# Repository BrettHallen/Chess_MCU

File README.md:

# Chess Microcontrollers
Tinkering with electronic chess games.  I'm am useless at chess but it still fascinates me.<br>

Related videos:
- [LogiChess Part 1](https://youtu.be/34F9DbmAjUU)
- [LogiChess Part 2](https://youtu.be/Y_kRFhx9leI)

## [Tandy 1650](/Tandy_1650_Chess)
Information about the Tandy 1650 Computerised Portable Sensory Chess game.  It uses the SciSys TE1 which is 4KB LogiChess implemented on an Hitachi HD6301V microcontroller.<br>

## [VIC-20 Chess Co-processor](/VIC-20_LogiChess)
I had a thought to re-use the MCU in the Tandy 1650, the SciSys TE1 implementing 4KB LogiChess, as a "co-processor" for vintage 8-bit computers, for example the Commodore VIC-20.<br>

This isn't the same as simply having the game code on a cartridge as the VIC's CPU is still running the code.<br>

I was wondering if it would be interesting to have a dedicated microcontroller doing the "chess processing".  It might be beyond my capabilities but this is how you learn new things.<br>

Ultimately it might be easier to just use an ATmega MCU with a chess program running on it.  But let's see.

## [LogiChess-Arduino Testing](/LogiChess-Arduino_Mega_Shield_Testing)
As part of my work on trying to get LogiChess MCU working with a VIC-20, I will first do some investigation on how to interface with the SciSys TE-1 by using an Arduino.  If I can get that working then it might give me some idea how to get it working on the VIC.<br>

## [Chess Keypad](/Chess_Keypad)
In conjunction with the Arduino interfacing, I'm creating a keypad to replicate the original Tandy 1650 hardware to assist with testing.<br>

So ...
- Step 1: get the SciSys TE1 working with my chess keypad and the Arduino logging information
- Step 2: get the Arduino (in place of the VIC-20) working with the SciSys TE1
- Step 3: get the VIC-20 working with the SciSys TE1

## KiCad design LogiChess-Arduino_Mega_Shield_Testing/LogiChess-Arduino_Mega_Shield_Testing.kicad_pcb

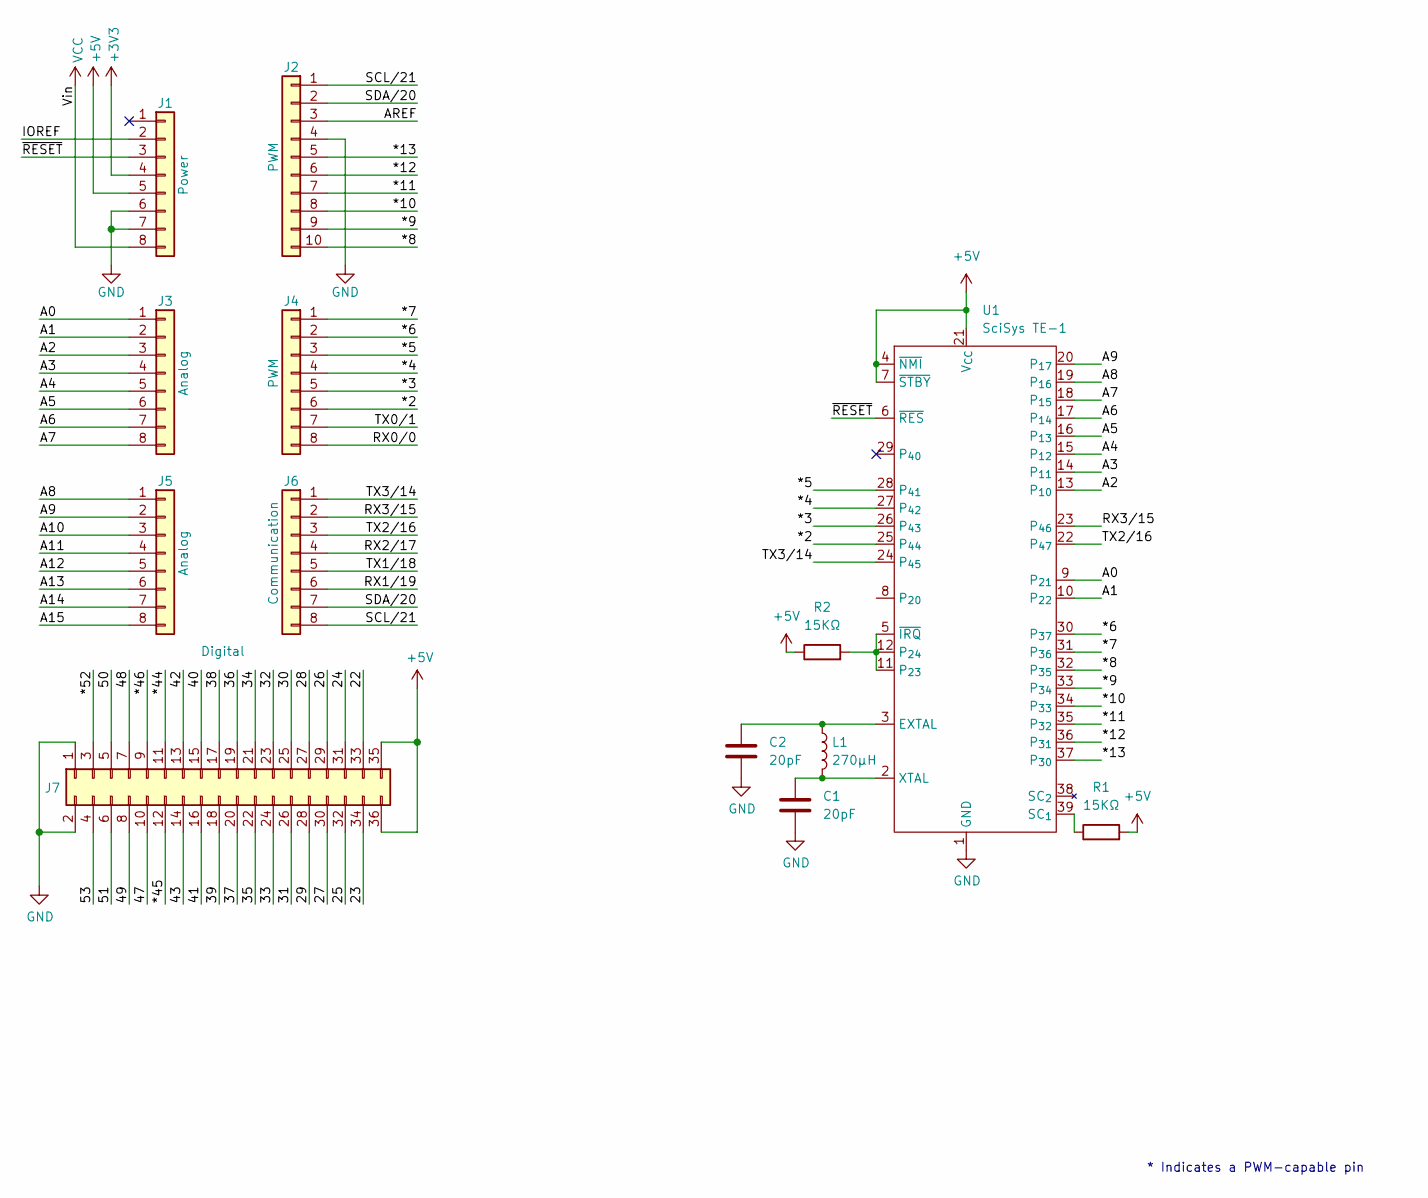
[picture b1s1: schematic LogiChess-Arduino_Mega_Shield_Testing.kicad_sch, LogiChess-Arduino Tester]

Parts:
C1, C2: 20pF; C_Disc_D3.8mm_W2.6mm_P2.50mm
J1: Power; PinSocket_1x08_P2.54mm_Vertical
J2: PWM; PinSocket_1x10_P2.54mm_Vertical
J3, J5: Analog; PinSocket_1x08_P2.54mm_Vertical
J4: PWM; PinSocket_1x08_P2.54mm_Vertical
J6: Communication; PinSocket_1x08_P2.54mm_Vertical
J7: Digital; PinSocket_2x18_P2.54mm_Vertical
L1: 270µH; L_Radial_D6.0mm_P4.00mm
R1, R2: 15KΩ; R_Axial_DIN0207_L6.3mm_D2.5mm_P7.62mm_Horizontal
U1: SciSys TE-1; DIP-40_W15.24mm

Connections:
+3V3: J1.4
+5V: J1.5, J7.35, J7.36, R1.2, R2.1, U1.4 (~NMI), U1.7 (~STBY), U1.21 (V_{CC})
/22: J7.33
/23: J7.34
/24: J7.31
/25: J7.32
/26: J7.29
/27: J7.30
/28: J7.27
/29: J7.28
/30: J7.25
/31: J7.26
/32: J7.23
/33: J7.24
/34: J7.21
/35: J7.22
/36: J7.19
/37: J7.20
/38: J7.17
/39: J7.18
/40: J7.15
/41: J7.16
/42: J7.13
/43: J7.14
/47: J7.10
/48: J7.7
/49: J7.8
/50: J7.5
/51: J7.6
/53: J7.4
/*2: J4.6, U1.25 (P_{44})
/*3: J4.5, U1.26 (P_{43})
/*4: J4.4, U1.27 (P_{42})
/*5: J4.3, U1.28 (P_{41})
/*6: J4.2, U1.30 (P_{37})
/*7: J4.1, U1.31 (P_{36})
/*8: J2.10, U1.32 (P_{35})
/*9: J2.9, U1.33 (P_{34})
/*10: J2.8, U1.34 (P_{33})
/*11: J2.7, U1.35 (P_{32})
/*12: J2.6, U1.36 (P_{31})
/*13: J2.5, U1.37 (P_{30})
/*44: J7.11
/*45: J7.12
/*46: J7.9
/*52: J7.3
/A0: J3.1, U1.9 (P_{21})
/A1: J3.2, U1.10 (P_{22})
/A2: J3.3, U1.13 (P_{10})
/A3: J3.4, U1.14 (P_{11})
/A4: J3.5, U1.15 (P_{12})
/A5: J3.6, U1.16 (P_{13})
/A6: J3.7, U1.17 (P_{14})
/A7: J3.8, U1.18 (P_{15})
/A8: J5.1, U1.19 (P_{16})
/A9: J5.2, U1.20 (P_{17})
/A10: J5.3
/A11: J5.4
/A12: J5.5
/A13: J5.6
/A14: J5.7
/A15: J5.8
/AREF: J2.3
/IOREF: J1.2
/RX0/0: J4.8
/RX1/19: J6.6
/RX2/17: J6.4
/RX3/15: J6.2, U1.23 (P_{46})
/SCL/21: J2.1, J6.8
/SDA/20: J2.2, J6.7
/TX0/1: J4.7
/TX1/18: J6.5
/TX2/16: J6.3, U1.22 (P_{47})
/TX3/14: J6.1, U1.24 (P_{45})
/~RESET: J1.3, U1.6 (~RES)
GND: C1.2, C2.2, J1.6, J1.7, J2.4, J7.1, J7.2, U1.1 (GND)
unnamed: C2.1, L1.1, U1.3 (EXTAL)
unnamed: R2.2, U1.5 (~IRQ), U1.11 (P_{23}), U1.12 (P_{24})
unnamed: R1.1, U1.39 (SC_{1})
unnamed: C1.1, L1.2, U1.2 (XTAL)
VCC: J1.8

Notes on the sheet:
* Indicates a PWM-capable pin

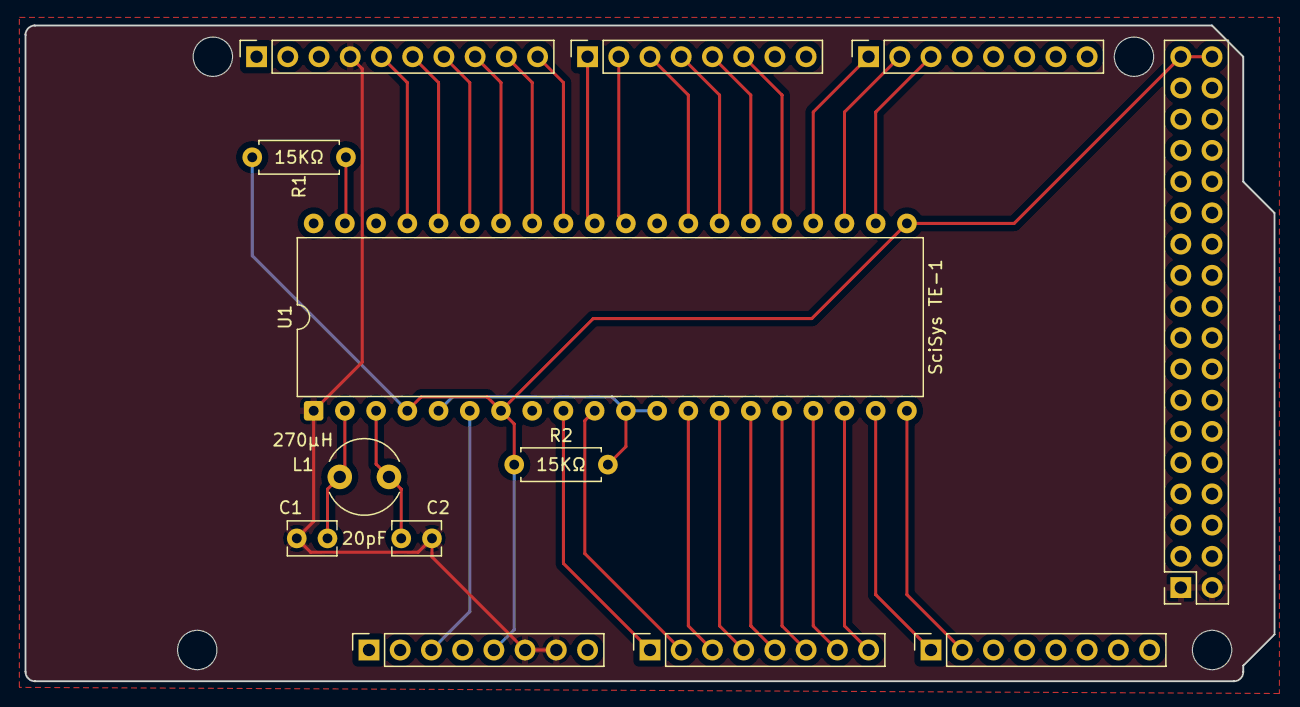
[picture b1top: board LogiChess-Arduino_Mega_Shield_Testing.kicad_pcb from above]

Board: 2 copper layers, 101.6 x 53.3 mm, 17 parts (0 on the bottom side), 34 nets.

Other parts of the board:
MH1, MH2, MH5, MH6: MountingHole_3.2mm

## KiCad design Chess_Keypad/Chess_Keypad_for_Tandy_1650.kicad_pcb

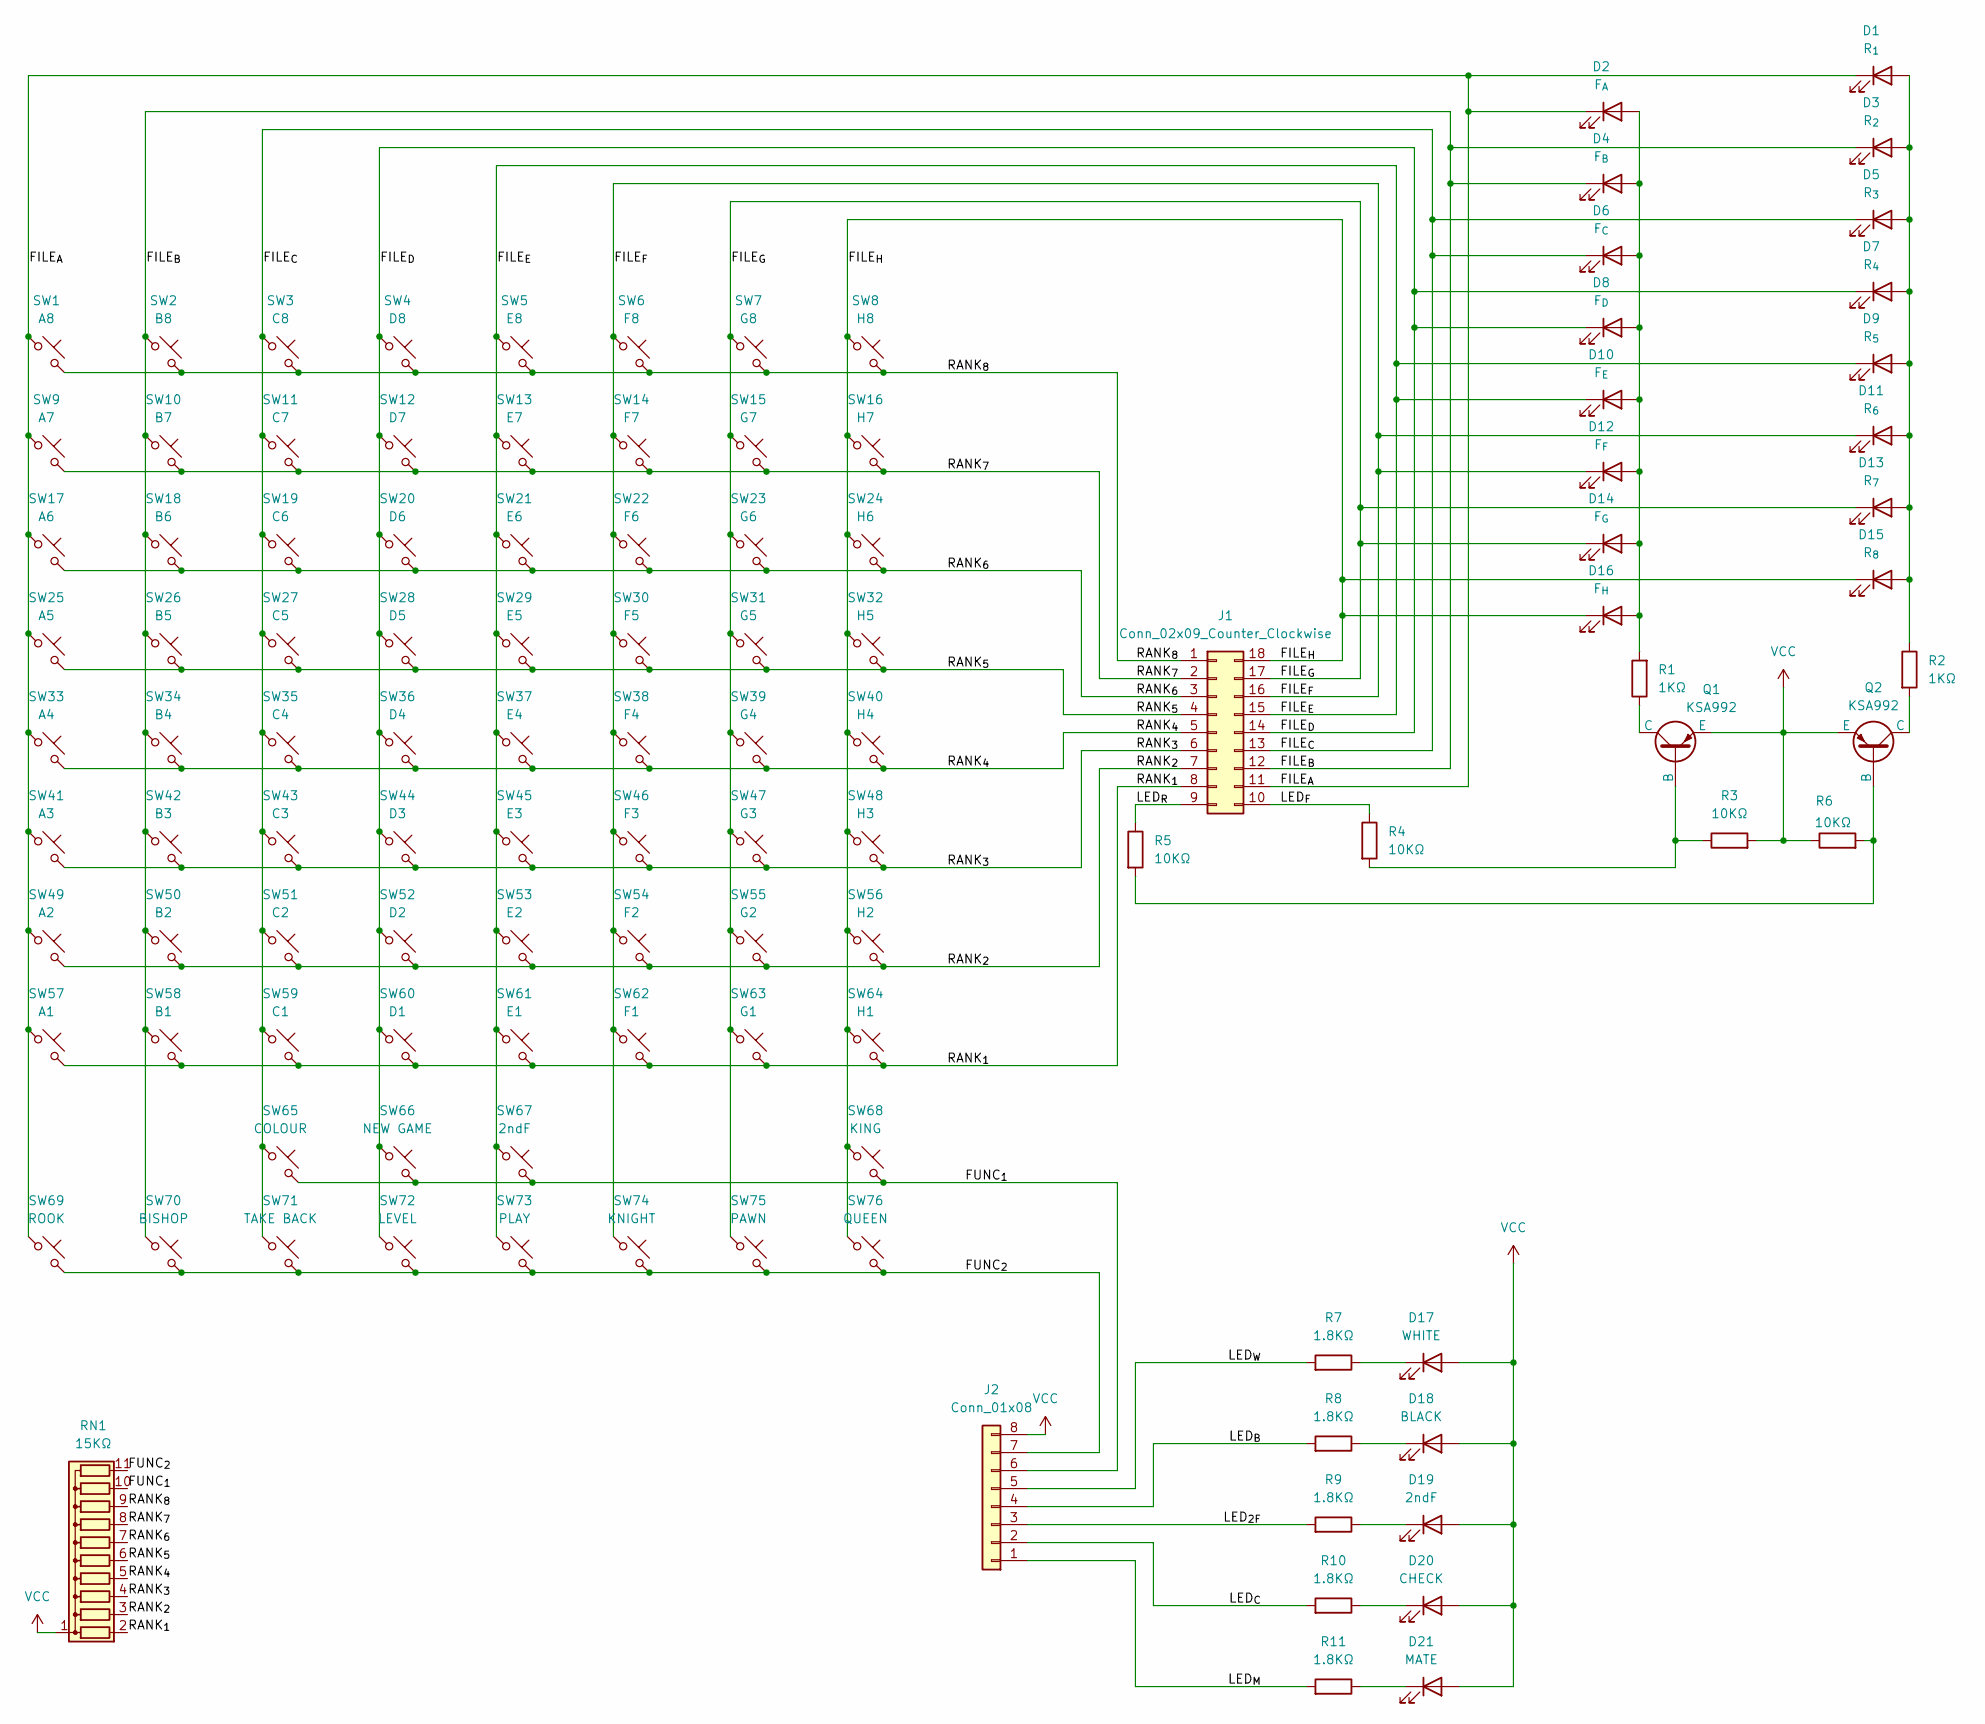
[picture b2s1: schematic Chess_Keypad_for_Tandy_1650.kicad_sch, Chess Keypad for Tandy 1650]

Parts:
D1: R_{1}; LED_D5.0mm
D2: F_{A}; LED_D5.0mm
D3: R_{2}; LED_D5.0mm
D4: F_{B}; LED_D5.0mm
D5: R_{3}; LED_D5.0mm
D6: F_{C}; LED_D5.0mm
D7: R_{4}; LED_D5.0mm
D8: F_{D}; LED_D5.0mm
D9: R_{5}; LED_D5.0mm
D10: F_{E}; LED_D5.0mm
D11: R_{6}; LED_D5.0mm
D12: F_{F}; LED_D5.0mm
D13: R_{7}; LED_D5.0mm
D14: F_{G}; LED_D5.0mm
D15: R_{8}; LED_D5.0mm
D16: F_{H}; LED_D5.0mm
D17: WHITE; LED_D5.0mm
D18: BLACK; LED_D5.0mm
D19: 2ndF; LED_D5.0mm
D20: CHECK; LED_D5.0mm
D21: MATE; LED_D5.0mm
J1: Conn_02x09_Counter_Clockwise; PinHeader_2x09_P2.54mm_Vertical
J2: Conn_01x08; PinHeader_1x08_P2.54mm_Vertical
Q1, Q2: KSA992; TO-92L
R1, R2: 1KΩ; R_Axial_DIN0207_L6.3mm_D2.5mm_P7.62mm_Horizontal
R3, R4, R5, R6: 10KΩ; R_Axial_DIN0207_L6.3mm_D2.5mm_P7.62mm_Horizontal
R7, R8, R9, R10, R11: 1.8KΩ; R_Axial_DIN0207_L6.3mm_D2.5mm_P7.62mm_Horizontal
RN1: 15KΩ; R_Array_SIP11
SW1: A8; SW_PUSH_6mm
SW2: B8; SW_PUSH_6mm
SW3: C8; SW_PUSH_6mm
SW4: D8; SW_PUSH_6mm
SW5: E8; SW_PUSH_6mm
SW6: F8; SW_PUSH_6mm
SW7: G8; SW_PUSH_6mm
SW8: H8; SW_PUSH_6mm
SW9: A7; SW_PUSH_6mm
SW10: B7; SW_PUSH_6mm
SW11: C7; SW_PUSH_6mm
SW12: D7; SW_PUSH_6mm
SW13: E7; SW_PUSH_6mm
SW14: F7; SW_PUSH_6mm
SW15: G7; SW_PUSH_6mm
SW16: H7; SW_PUSH_6mm
SW17: A6; SW_PUSH_6mm
SW18: B6; SW_PUSH_6mm
SW19: C6; SW_PUSH_6mm
SW20: D6; SW_PUSH_6mm
SW21: E6; SW_PUSH_6mm
SW22: F6; SW_PUSH_6mm
SW23: G6; SW_PUSH_6mm
SW24: H6; SW_PUSH_6mm
SW25: A5; SW_PUSH_6mm
SW26: B5; SW_PUSH_6mm
SW27: C5; SW_PUSH_6mm
SW28: D5; SW_PUSH_6mm
SW29: E5; SW_PUSH_6mm
SW30: F5; SW_PUSH_6mm
SW31: G5; SW_PUSH_6mm
SW32: H5; SW_PUSH_6mm
SW33: A4; SW_PUSH_6mm
SW34: B4; SW_PUSH_6mm
SW35: C4; SW_PUSH_6mm
SW36: D4; SW_PUSH_6mm
SW37: E4; SW_PUSH_6mm
SW38: F4; SW_PUSH_6mm
SW39: G4; SW_PUSH_6mm
SW40: H4; SW_PUSH_6mm
SW41: A3; SW_PUSH_6mm
SW42: B3; SW_PUSH_6mm
SW43: C3; SW_PUSH_6mm
SW44: D3; SW_PUSH_6mm
SW45: E3; SW_PUSH_6mm
SW46: F3; SW_PUSH_6mm
SW47: G3; SW_PUSH_6mm
SW48: H3; SW_PUSH_6mm
SW49: A2; SW_PUSH_6mm
SW50: B2; SW_PUSH_6mm
SW51: C2; SW_PUSH_6mm
SW52: D2; SW_PUSH_6mm
SW53: E2; SW_PUSH_6mm
SW54: F2; SW_PUSH_6mm
SW55: G2; SW_PUSH_6mm
SW56: H2; SW_PUSH_6mm
SW57: A1; SW_PUSH_6mm
SW58: B1; SW_PUSH_6mm
SW59: C1; SW_PUSH_6mm
SW60: D1; SW_PUSH_6mm
SW61: E1; SW_PUSH_6mm
SW62: F1; SW_PUSH_6mm
SW63: G1; SW_PUSH_6mm
SW64: H1; SW_PUSH_6mm
SW65: COLOUR; SW_PUSH_6mm
SW66: NEW GAME; SW_PUSH_6mm
SW67: 2ndF; SW_PUSH_6mm
SW68: KING; SW_PUSH_6mm
SW69: ROOK; SW_PUSH_6mm
SW70: BISHOP; SW_PUSH_6mm
SW71: TAKE BACK; SW_PUSH_6mm
SW72: LEVEL; SW_PUSH_6mm
SW73: PLAY; SW_PUSH_6mm
SW74: KNIGHT; SW_PUSH_6mm
SW75: PAWN; SW_PUSH_6mm
SW76: QUEEN; SW_PUSH_6mm

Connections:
/FILE_{A}: D1.1 (K), D2.1 (K), J1.11, SW1.1, SW9.1, SW17.1, SW25.1, SW33.1, SW41.1, SW49.1, SW57.1, SW69.1
/FILE_{B}: D3.1 (K), D4.1 (K), J1.12, SW2.1, SW10.1, SW18.1, SW26.1, SW34.1, SW42.1, SW50.1, SW58.1, SW70.1
/FILE_{C}: D5.1 (K), D6.1 (K), J1.13, SW3.1, SW11.1, SW19.1, SW27.1, SW35.1, SW43.1, SW51.1, SW59.1, SW65.1, SW71.1
/FILE_{D}: D7.1 (K), D8.1 (K), J1.14, SW4.1, SW12.1, SW20.1, SW28.1, SW36.1, SW44.1, SW52.1, SW60.1, SW66.1, SW72.1
/FILE_{E}: D9.1 (K), D10.1 (K), J1.15, SW5.1, SW13.1, SW21.1, SW29.1, SW37.1, SW45.1, SW53.1, SW61.1, SW67.1, SW73.1
/FILE_{F}: D11.1 (K), D12.1 (K), J1.16, SW6.1, SW14.1, SW22.1, SW30.1, SW38.1, SW46.1, SW54.1, SW62.1, SW74.1
/FILE_{G}: D13.1 (K), D14.1 (K), J1.17, SW7.1, SW15.1, SW23.1, SW31.1, SW39.1, SW47.1, SW55.1, SW63.1, SW75.1
/FILE_{H}: D15.1 (K), D16.1 (K), J1.18, SW8.1, SW16.1, SW24.1, SW32.1, SW40.1, SW48.1, SW56.1, SW64.1, SW68.1, SW76.1
/FUNC_{1}: J2.6, RN1.10 (R9), SW65.2, SW66.2, SW67.2, SW68.2
/FUNC_{2}: J2.7, RN1.11 (R10), SW69.2, SW70.2, SW71.2, SW72.2, SW73.2, SW74.2, SW75.2, SW76.2
/LED_{2F}: J2.3, R9.2
/LED_{B}: J2.4, R8.2
/LED_{C}: J2.2, R10.2
/LED_{F}: J1.10, R4.1
/LED_{M}: J2.1, R11.2
/LED_{R}: J1.9, R5.1
/LED_{W}: J2.5, R7.2
/RANK_{1}: J1.8, RN1.2 (R1), SW57.2, SW58.2, SW59.2, SW60.2, SW61.2, SW62.2, SW63.2, SW64.2
/RANK_{2}: J1.7, RN1.3 (R2), SW49.2, SW50.2, SW51.2, SW52.2, SW53.2, SW54.2, SW55.2, SW56.2
/RANK_{3}: J1.6, RN1.4 (R3), SW41.2, SW42.2, SW43.2, SW44.2, SW45.2, SW46.2, SW47.2, SW48.2
/RANK_{4}: J1.5, RN1.5 (R4), SW33.2, SW34.2, SW35.2, SW36.2, SW37.2, SW38.2, SW39.2, SW40.2
/RANK_{5}: J1.4, RN1.6 (R5), SW25.2, SW26.2, SW27.2, SW28.2, SW29.2, SW30.2, SW31.2, SW32.2
/RANK_{6}: J1.3, RN1.7 (R6), SW17.2, SW18.2, SW19.2, SW20.2, SW21.2, SW22.2, SW23.2, SW24.2
/RANK_{7}: J1.2, RN1.8 (R7), SW9.2, SW10.2, SW11.2, SW12.2, SW13.2, SW14.2, SW15.2, SW16.2
/RANK_{8}: J1.1, RN1.9 (R8), SW1.2, SW2.2, SW3.2, SW4.2, SW5.2, SW6.2, SW7.2, SW8.2
unnamed: D1.2 (A), D3.2 (A), D5.2 (A), D7.2 (A), D9.2 (A), D11.2 (A), D13.2 (A), D15.2 (A), R2.1
unnamed: D2.2 (A), D4.2 (A), D6.2 (A), D8.2 (A), D10.2 (A), D12.2 (A), D14.2 (A), D16.2 (A), R1.2
unnamed: D17.1 (K), R7.1
unnamed: D18.1 (K), R8.1
unnamed: D19.1 (K), R9.1
unnamed: D20.1 (K), R10.1
unnamed: D21.1 (K), R11.1
unnamed: Q1.2 (B), R3.1, R4.2
unnamed: Q1.1 (C), R1.1
unnamed: Q2.2 (B), R5.2, R6.2
unnamed: Q2.1 (C), R2.2
VCC: D17.2 (A), D18.2 (A), D19.2 (A), D20.2 (A), D21.2 (A), J2.8, Q1.3 (E), Q2.3 (E), R3.2, R6.1, RN1.1 (common)

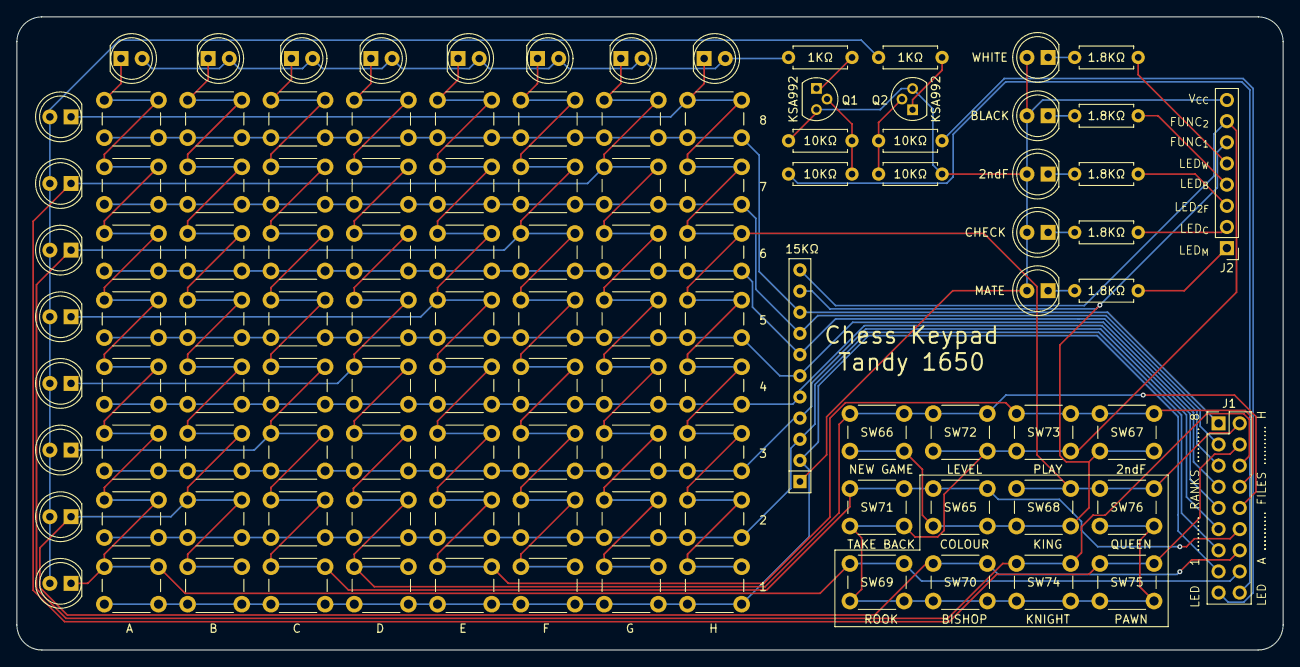
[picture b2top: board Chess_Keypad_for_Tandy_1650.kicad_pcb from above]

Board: 2 copper layers, 152.0 x 76.0 mm, 113 parts (0 on the bottom side), 37 nets.

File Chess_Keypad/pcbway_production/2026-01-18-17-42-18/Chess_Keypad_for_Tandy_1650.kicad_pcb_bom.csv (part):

Designator,Quantity,Value,Footprint,Package,MPN,DNP,Mount_Type,Description,Sim.Pins,Sim.Device,Sim.Type
D1,1,R_{1},LED_D5.0mm,,,,tht,Light emitting diode,1=K 2=A,,
D10,1,F_{E},LED_D5.0mm,,,,tht,Light emitting diode,1=K 2=A,,
D11,1,R_{6},LED_D5.0mm,,,,tht,Light emitting diode,1=K 2=A,,
D12,1,F_{F},LED_D5.0mm,,,,tht,Light emitting diode,1=K 2=A,,
D13,1,R_{7},LED_D5.0mm,,,,tht,Light emitting diode,1=K 2=A,,
D14,1,F_{G},LED_D5.0mm,,,,tht,Light emitting diode,1=K 2=A,,
D15,1,R_{8},LED_D5.0mm,,,,tht,Light emitting diode,1=K 2=A,,
D16,1,F_{H},LED_D5.0mm,,,,tht,Light emitting diode,1=K 2=A,,
D17,1,WHITE,LED_D5.0mm,,,,tht,Light emitting diode,1=K 2=A,,
D18,1,BLACK,LED_D5.0mm,,,,tht,Light emitting diode,1=K 2=A,,
D19,1,2ndF,LED_D5.0mm,,,,tht,Light emitting diode,1=K 2=A,,
D2,1,F_{A},LED_D5.0mm,,,,tht,Light emitting diode,1=K 2=A,,
D20,1,CHECK,LED_D5.0mm,,,,tht,Light emitting diode,1=K 2=A,,
D21,1,MATE,LED_D5.0mm,,,,tht,Light emitting diode,1=K 2=A,,
D3,1,R_{2},LED_D5.0mm,,,,tht,Light emitting diode,1=K 2=A,,
D4,1,F_{B},LED_D5.0mm,,,,tht,Light emitting diode,1=K 2=A,,
D5,1,R_{3},LED_D5.0mm,,,,tht,Light emitting diode,1=K 2=A,,
D6,1,F_{C},LED_D5.0mm,,,,tht,Light emitting diode,1=K 2=A,,
D7,1,R_{4},LED_D5.0mm,,,,tht,Light emitting diode,1=K 2=A,,
D8,1,F_{D},LED_D5.0mm,,,,tht,Light emitting diode,1=K 2=A,,
D9,1,R_{5},LED_D5.0mm,,,,tht,Light emitting diode,1=K 2=A,,
J1,1,Conn_02x09_Counter_Clockwise,PinHeader_2x09_P2.54mm_Vertical,,,,tht,"Generic connector, double row, 02x09, counter clockwise pin numbering scheme (similar to DIP package numbering), script generated (kicad-library-utils/schlib/autogen/connector/)",,,
J2,1,Conn_01x08,PinHeader_1x08_P2.54mm_Vertical,,,,tht,"Generic connector, single row, 01x08, script generated (kicad-library-utils/schlib/autogen/connector/)",,,
"Q1, Q2",2,KSA992,TO-92L,,,,tht,"Bipolar transistor symbol for simulation only, substrate tied to the emitter",1=C 2=B 3=E,PNP,GUMMELPOON
"R1, R2",2,1KΩ,R_Axial_DIN0207_L6.3mm_D2.5mm_P7.62mm_Horizontal,,,,tht,Resistor,,,
"R10, R11, R7, R8, R9",5,1.8KΩ,R_Axial_DIN0207_L6.3mm_D2.5mm_P7.62mm_Horizontal,,,,tht,Resistor,,,
"R3, R4, R5, R6",4,10KΩ,R_Axial_DIN0207_L6.3mm_D2.5mm_P7.62mm_Horizontal,,,,tht,Resistor,,,
RN1,1,15KΩ,R_Array_SIP11,,,,tht,"10 resistor network, star topology, bussed resistors, small symbol",,,
SW1,1,A8,SW_PUSH_6mm,,,,tht,"Push button switch, normally open, two pins, 45° tilted",,,
SW10,1,B7,SW_PUSH_6mm,,,,tht,"Push button switch, normally open, two pins, 45° tilted",,,
SW11,1,C7,SW_PUSH_6mm,,,,tht,"Push button switch, normally open, two pins, 45° tilted",,,
SW12,1,D7,SW_PUSH_6mm,,,,tht,"Push button switch, normally open, two pins, 45° tilted",,,
SW13,1,E7,SW_PUSH_6mm,,,,tht,"Push button switch, normally open, two pins, 45° tilted",,,
SW14,1,F7,SW_PUSH_6mm,,,,tht,"Push button switch, normally open, two pins, 45° tilted",,,
SW15,1,G7,SW_PUSH_6mm,,,,tht,"Push button switch, normally open, two pins, 45° tilted",,,
SW16,1,H7,SW_PUSH_6mm,,,,tht,"Push button switch, normally open, two pins, 45° tilted",,,
SW17,1,A6,SW_PUSH_6mm,,,,tht,"Push button switch, normally open, two pins, 45° tilted",,,
SW18,1,B6,SW_PUSH_6mm,,,,tht,"Push button switch, normally open, two pins, 45° tilted",,,
SW19,1,C6,SW_PUSH_6mm,,,,tht,"Push button switch, normally open, two pins, 45° tilted",,,
SW2,1,B8,SW_PUSH_6mm,,,,tht,"Push button switch, normally open, two pins, 45° tilted",,,
SW20,1,D6,SW_PUSH_6mm,,,,tht,"Push button switch, normally open, two pins, 45° tilted",,,
SW21,1,E6,SW_PUSH_6mm,,,,tht,"Push button switch, normally open, two pins, 45° tilted",,,
SW22,1,F6,SW_PUSH_6mm,,,,tht,"Push button switch, normally open, two pins, 45° tilted",,,
SW23,1,G6,SW_PUSH_6mm,,,,tht,"Push button switch, normally open, two pins, 45° tilted",,,
SW24,1,H6,SW_PUSH_6mm,,,,tht,"Push button switch, normally open, two pins, 45° tilted",,,
SW25,1,A5,SW_PUSH_6mm,,,,tht,"Push button switch, normally open, two pins, 45° tilted",,,
SW26,1,B5,SW_PUSH_6mm,,,,tht,"Push button switch, normally open, two pins, 45° tilted",,,
SW27,1,C5,SW_PUSH_6mm,,,,tht,"Push button switch, normally open, two pins, 45° tilted",,,
SW28,1,D5,SW_PUSH_6mm,,,,tht,"Push button switch, normally open, two pins, 45° tilted",,,
SW29,1,E5,SW_PUSH_6mm,,,,tht,"Push button switch, normally open, two pins, 45° tilted",,,
SW3,1,C8,SW_PUSH_6mm,,,,tht,"Push button switch, normally open, two pins, 45° tilted",,,
SW30,1,F5,SW_PUSH_6mm,,,,tht,"Push button switch, normally open, two pins, 45° tilted",,,
SW31,1,G5,SW_PUSH_6mm,,,,tht,"Push button switch, normally open, two pins, 45° tilted",,,
SW32,1,H5,SW_PUSH_6mm,,,,tht,"Push button switch, normally open, two pins, 45° tilted",,,
SW33,1,A4,SW_PUSH_6mm,,,,tht,"Push button switch, normally open, two pins, 45° tilted",,,
SW34,1,B4,SW_PUSH_6mm,,,,tht,"Push button switch, normally open, two pins, 45° tilted",,,
SW35,1,C4,SW_PUSH_6mm,,,,tht,"Push button switch, normally open, two pins, 45° tilted",,,
SW36,1,D4,SW_PUSH_6mm,,,,tht,"Push button switch, normally open, two pins, 45° tilted",,,
SW37,1,E4,SW_PUSH_6mm,,,,tht,"Push button switch, normally open, two pins, 45° tilted",,,
SW38,1,F4,SW_PUSH_6mm,,,,tht,"Push button switch, normally open, two pins, 45° tilted",,,
SW39,1,G4,SW_PUSH_6mm,,,,tht,"Push button switch, normally open, two pins, 45° tilted",,,
SW4,1,D8,SW_PUSH_6mm,,,,tht,"Push button switch, normally open, two pins, 45° tilted",,,
SW40,1,H4,SW_PUSH_6mm,,,,tht,"Push button switch, normally open, two pins, 45° tilted",,,
SW41,1,A3,SW_PUSH_6mm,,,,tht,"Push button switch, normally open, two pins, 45° tilted",,,
SW42,1,B3,SW_PUSH_6mm,,,,tht,"Push button switch, normally open, two pins, 45° tilted",,,
SW43,1,C3,SW_PUSH_6mm,,,,tht,"Push button switch, normally open, two pins, 45° tilted",,,
SW44,1,D3,SW_PUSH_6mm,,,,tht,"Push button switch, normally open, two pins, 45° tilted",,,
SW45,1,E3,SW_PUSH_6mm,,,,tht,"Push button switch, normally open, two pins, 45° tilted",,,
SW46,1,F3,SW_PUSH_6mm,,,,tht,"Push button switch, normally open, two pins, 45° tilted",,,
SW47,1,G3,SW_PUSH_6mm,,,,tht,"Push button switch, normally open, two pins, 45° tilted",,,
SW48,1,H3,SW_PUSH_6mm,,,,tht,"Push button switch, normally open, two pins, 45° tilted",,,
SW49,1,A2,SW_PUSH_6mm,,,,tht,"Push button switch, normally open, two pins, 45° tilted",,,
SW5,1,E8,SW_PUSH_6mm,,,,tht,"Push button switch, normally open, two pins, 45° tilted",,,
SW50,1,B2,SW_PUSH_6mm,,,,tht,"Push button switch, normally open, two pins, 45° tilted",,,
SW51,1,C2,SW_PUSH_6mm,,,,tht,"Push button switch, normally open, two pins, 45° tilted",,,
SW52,1,D2,SW_PUSH_6mm,,,,tht,"Push button switch, normally open, two pins, 45° tilted",,,
SW53,1,E2,SW_PUSH_6mm,,,,tht,"Push button switch, normally open, two pins, 45° tilted",,,
SW54,1,F2,SW_PUSH_6mm,,,,tht,"Push button switch, normally open, two pins, 45° tilted",,,
SW55,1,G2,SW_PUSH_6mm,,,,tht,"Push button switch, normally open, two pins, 45° tilted",,,
SW56,1,H2,SW_PUSH_6mm,,,,tht,"Push button switch, normally open, two pins, 45° tilted",,,
SW57,1,A1,SW_PUSH_6mm,,,,tht,"Push button switch, normally open, two pins, 45° tilted",,,
SW58,1,B1,SW_PUSH_6mm,,,,tht,"Push button switch, normally open, two pins, 45° tilted",,,
SW59,1,C1,SW_PUSH_6mm,,,,tht,"Push button switch, normally open, two pins, 45° tilted",,,
SW6,1,F8,SW_PUSH_6mm,,,,tht,"Push button switch, normally open, two pins, 45° tilted",,,
SW60,1,D1,SW_PUSH_6mm,,,,tht,"Push button switch, normally open, two pins, 45° tilted",,,
SW61,1,E1,SW_PUSH_6mm,,,,tht,"Push button switch, normally open, two pins, 45° tilted",,,
SW62,1,F1,SW_PUSH_6mm,,,,tht,"Push button switch, normally open, two pins, 45° tilted",,,
SW63,1,G1,SW_PUSH_6mm,,,,tht,"Push button switch, normally open, two pins, 45° tilted",,,
SW64,1,H1,SW_PUSH_6mm,,,,tht,"Push button switch, normally open, two pins, 45° tilted",,,
SW65,1,COLOUR,SW_PUSH_6mm,,,,tht,"Push button switch, normally open, two pins, 45° tilted",,,
SW66,1,NEW GAME,SW_PUSH_6mm,,,,tht,"Push button switch, normally open, two pins, 45° tilted",,,
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
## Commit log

2026-01-10 Design started
2026-01-11 Added estimated L1 inductance
2026-01-15 Corrected function LED orientation
2026-01-15 Rename folder
2026-01-15 Design work started
2026-01-15 Renamed project
2026-01-15 Work in progress
2026-01-18 Completed initial design
2026-01-18 Finalised initial design
2026-01-18 Initial design of Arduino shield
